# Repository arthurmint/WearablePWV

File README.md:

# WearablePWV
A wearable, wireless sensor for measuring pulse-wave velocity in humans

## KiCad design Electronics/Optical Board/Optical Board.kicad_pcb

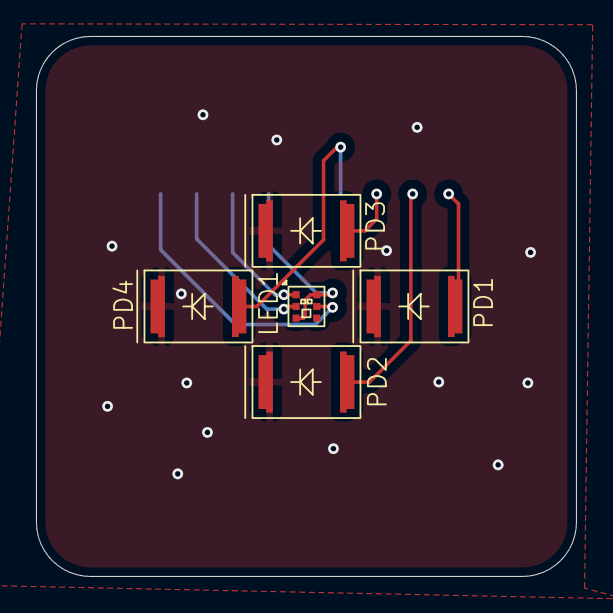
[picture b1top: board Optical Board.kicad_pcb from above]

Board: 2 copper layers, 30.0 x 30.0 mm, 6 parts (1 on the bottom side), 9 nets.

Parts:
J2: OPTICAL; JST_PH_S9B-PH-SM4-TB_1x09-1MP_P2.00mm_Horizontal
LED1: SFH-7016; SFH-7016 Multi Chip LED
PD1, PD2, PD3, PD4: SFH2200; TOPLED D5140

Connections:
+3V3: J2.4, LED1.2 (A), LED1.5 (A)
/LED1: J2.3, LED1.1 (KIR)
/LED2: J2.2, LED1.3 (KGREEN)
/LED3: J2.1, LED1.4 (KRED)
/PD1: J2.9, PD1.2 (A)
/PD2: J2.8, PD2.2 (A)
/PD3: J2.7, PD3.2 (A)
/PD4: J2.6, PD4.2 (A)
/PD_K: J2.5, PD1.1 (K), PD2.1 (K), PD3.1 (K), PD4.1 (K)

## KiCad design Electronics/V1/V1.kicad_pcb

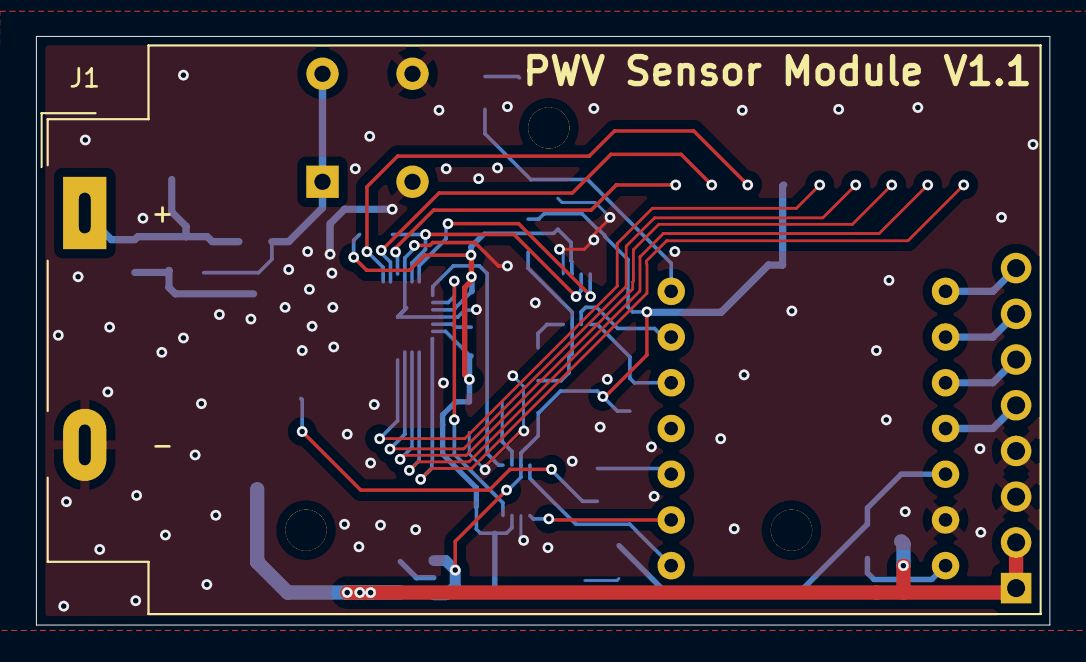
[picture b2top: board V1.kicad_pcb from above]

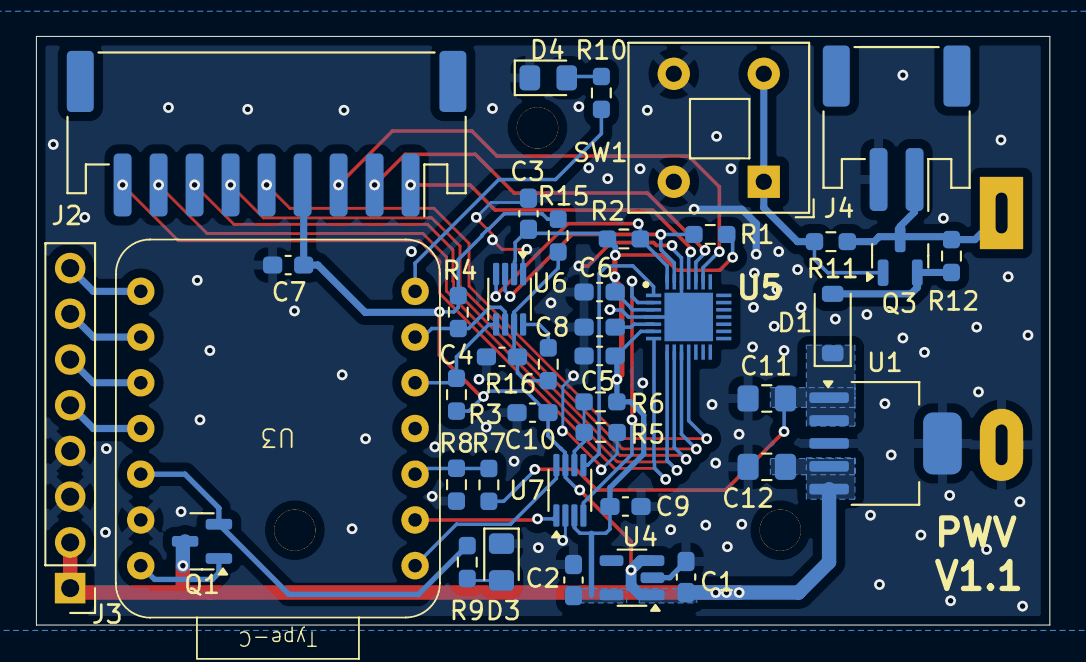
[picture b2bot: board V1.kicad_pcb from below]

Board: 2 copper layers, 56.3 x 32.7 mm, 42 parts (41 on the bottom side), 37 nets.

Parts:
C1, C8: 1u; C_0603_1608Metric_Pad1.08x0.95mm_HandSolder
C2: 10u; C_0603_1608Metric_Pad1.08x0.95mm_HandSolder
C3, C4, C5, C6, C9, C10: 100n; C_0603_1608Metric_Pad1.08x0.95mm_HandSolder
C7: 4u7; C_0603_1608Metric_Pad1.08x0.95mm_HandSolder
C11, C12: 10uF; C_0805_2012Metric_Pad1.18x1.45mm_HandSolder
D1: B130LAW-7-F; D_SOD-123
D3: 3V3 LED; LED_0805_2012Metric_Pad1.15x1.40mm_HandSolder
D4: CTRL LED; LED_0805_2012Metric_Pad1.15x1.40mm_HandSolder
J1: BA9VPC; BatteryHolder_MPD_BA9VPC_1xPP3
J2: OPTICAL; JST_PH_S9B-PH-SM4-TB_1x09-1MP_P2.00mm_Horizontal
J3: GPIO; PinHeader_1x08_P2.54mm_Vertical
J4: JST; JST_PH_S2B-PH-SM4-TB_1x02-1MP_P2.00mm_Horizontal
Q1, Q3: PMV41XPAR; SOT-23
R1, R2, R3, R4, R8, R11: 10k; R_0603_1608Metric_Pad0.98x0.95mm_HandSolder
R5: 200k; R_0603_1608Metric_Pad0.98x0.95mm_HandSolder
R6, R12: 0R; R_0603_1608Metric_Pad0.98x0.95mm_HandSolder
R7: 20k; R_0603_1608Metric_Pad0.98x0.95mm_HandSolder
R9, R10: 330; R_0603_1608Metric_Pad0.98x0.95mm_HandSolder
R15: 200K; R_0603_1608Metric_Pad0.98x0.95mm_HandSolder
R16: 0; R_0603_1608Metric_Pad0.98x0.95mm_HandSolder
SW1: PVA1 EE H1 3.5N V2; SW_Push_2P1T_Toggle_CK_PVA1xxH1xxxxxxV2
U1: TPS7A4533; SOT-223-6
U3: XIAO-ESP32-C3; Seeed Studio XIAO ESP32-C3
U4: TPS72218; SOT-23-5
U5: ADPD1080
U6: PCA9306DC; VSSOP-8_2.3x2mm_P0.5mm
U7: TXB0102DCU; VSSOP-8_2.3x2mm_P0.5mm

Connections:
+1V8: C2.1, C3.1, C5.1, C6.1, C9.1, R1.1, R2.1, R6.1, U4.5 (VOUT), U5.3 (DVDD), U5.6 (AVDD), U6.2 (VREF1), U7.3 (VCCA)
+3V3: C1.1, C7.1, C10.1, C12.1, J2.4, J3.1, J3.2, Q1.3 (D), R3.1, R4.1, R15.1, U1.4 (OUT), U1.5 (ADJ), U4.1 (VIN), U4.3 (EN), U7.7 (VCCB)
/AFE_0: U5.1 (GPIO0), U7.5 (A1)
/AFE_1: U5.2 (GPIO1), U7.4 (A2)
/BAT+: J1.1, J4.1, Q3.3 (D), R11.1, R12.1
/BAT_SENSE: R7.2, R8.1, U3.3 (D2)
/LED1: J2.3, U5.23 (LEDX1)
/LED2: J2.2, U5.24 (LEDX2)
/LED3: J2.1, U5.25 (LEDX3)
/PD1: J2.9, U5.7 (PD1)
/PD2: J2.8, U5.8 (PD2)
/PD3: J2.7, U5.9 (PD3)
/PD4: J2.6, U5.10 (PD4)
/PD_K: J2.5, U5.11 (PDC)
/PPG_SCL: R1.2, U5.27 (SCL), U6.3 (SCL1)
/PPG_SDA: R2.2, U5.28 (SDA), U6.4 (SDA1)
/UC_D0: U3.1 (D0), U7.8 (B1)
/UC_D1: U3.2 (D1), U7.1 (B2)
/UC_D6: R10.1, U3.7 (D6/TX)
/UC_D7: J3.8, U3.8 (D7/RX)
/UC_D8: J3.7, U3.9 (D8/SCK)
/UC_D9: J3.6, U3.10 (D9/MISO)
/UC_D10: J3.5, U3.11 (D10/MOSI)
/UC_SCL: R4.2, U3.6 (D5/SCL), U6.6 (SCL2)
/UC_SDA: R3.2, U3.5 (D4/SDA), U6.5 (SDA2)
GND: C1.2, C2.2, C3.2, C4.2, C5.2, C6.2, C7.2, C8.2, C9.2, C10.2, C11.2, C12.2, D3.1 (K), D4.1 (K), J1.2, J3.3, J3.4, J4.2, R5.2, R8.2, SW1.2, SW1.4, U1.3 (GND), U1.6 (GND), U3.13 (GND), U4.2 (GND), U5.4 (AGND), U5.26 (LGND), U5.29 (DGND), U6.1 (GND), U7.2 (GND)
unnamed: D1.2 (A), Q3.2 (S), R12.2
unnamed: D3.2 (A), R9.2
unnamed: D4.2 (A), R10.2
unnamed: Q1.2 (S), R9.1, U3.12 (3V3)
unnamed: Q3.1 (G), R11.2, SW1.1, SW1.3
unnamed: C8.1, U5.5 (VREF)
unnamed: R16.2, U6.8 (EN)
unnamed: C4.1, R15.2, R16.1, U6.7 (VREF2)
unnamed: R5.1, R6.2, U7.6 (OE)
VBAT: C11.1, D1.1 (K), R7.1, U1.1 (~SHDN), U1.2 (IN)
VUSB: Q1.1 (G), U3.14 (5V)

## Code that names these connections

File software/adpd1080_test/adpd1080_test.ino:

//working code
#include <Arduino.h>

#include "../include/pinout.h"
#include "../include/adpd1080.h"

ADPD1080 AFE;
uint32_t data;
/* Project specific functions -- define measurement procedure */

bool startMeasurement() {
  if (AFE.getMode() == AFE.STANDBY) {
    if (!AFE.clk32k_en(1)) {
      AFE.configurePPG(false); // configures and sets OPERATION internally
      // Now flush the FIFO after configuration
      AFE.setMode(AFE.PROGRAM);
      delay(10);
      AFE.setMode(AFE.OPERATION);
    }
    return false;

  } else if (AFE.getMode() == AFE.PROGRAM) {
    AFE.setMode(AFE.OPERATION);
    return false;

  } else {
    #ifdef DEBUG_OUTPUT
    Serial.println("Device not in STANDBY, cannot start measurement");
    #endif
    return true;
  }
}

void setup() { 
    Serial.begin(9600);
    delay(1000);
    
    AFE.begin(PIN_SDA, PIN_SCL, PIN_GPIO0, PIN_GPIO1);
    delay(500);
    
    AFE.printDevID(); // must be after begin()
    
    startMeasurement();
    AFE.readbackConfig(); 
  Serial.println("Initialised ADPD1080");
  //delay(10000);
}

void loop() {
  //uint16_t pd1, pd2, pd3, pd4;

  uint16_t available_data = (AFE.getStatus() >> 8) & 0xFF;
  //Serial.print("Available data: ");
  //Serial.print(available_data);

  if (available_data >= 4) {
    AFE.readFIFO(&data, 4);

    Serial.println(data);
    /*
    if (!AFE.readPPG(&pd1, &pd2, &pd3, &pd4)) {
      Serial.print(" PD1: "); Serial.print(pd1);
      Serial.print(" PD2: "); Serial.print(pd2);
      Serial.print(" PD3: "); Serial.print(pd3);
      Serial.print(" PD4: "); Serial.println(pd4);
    } else {
      Serial.println("Read error");
    }*/

    
  } else {
    //Serial.println(" - Not enough data");
  }

  delay(100);
}

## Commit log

2025-11-06 Added symbol for Xiao ESP32
2025-11-09 Added more symbols
2025-11-13 added capacitors and pull-up resistors
2025-11-14 Added footprint for ADPD144
2025-11-19 Added more symbols and footprints
2025-11-25 Added footprints for SFH-7016 and TOPLED
2025-11-25 Added level shifter for gpio, 5V reg, battery monitor and changed some footprints.
2025-11-27 Added Seeed Studio footprint
2025-12-03 Minor fixes
2025-12-05 Some unfinished PCB changes
2025-12-05 minor changes
2025-12-05 Swapped I2C shifter for PCA9306DC
2025-12-07 Changing from integrated optical sensors to separate PCB
2025-12-23 Footprint changes
2026-02-09 Add files via upload
    software files
2026-02-25 Work-in-progress, added pinout.h and test script
2026-02-26 adpd1080.h
2026-03-15 startMeasurement
2026-03-24 Progress with adpd1080, just need LED and photodiode headers
2026-04-03 LED pulse working, interrupt and polling reading added but not yet working.
2026-04-04 Create espseeed_host
2026-04-04 Create gg
2026-04-04 Untested: TIA ADC Mode. WIP
2026-04-06 Added some helpful comments to adpd1080.h
2026-04-06 Updated ,gitignore with .vscode
2026-04-06 Made it so that you can open pwvdissertation.ino in Arduino IDE
2026-04-08 Made setLED() more readable
2026-04-08 Added latency measurements to espseeed_host
2026-04-08 Small fixes to adpd1080.h
2026-04-08 Back in time
2026-04-16 PDs reading successfully
2026-04-21 Try different AFE connection
2026-04-29 Added Python Serial logging / plotting scripts and setup instructions
2026-04-29 Changes to the ADPD1080 to prevent it from saturating, see logbook
2026-05-10 Removed limits
2026-05-10 Average baseline readings
2026-05-10 Web Server changes
2026-05-10 Dual graph
2026-05-11 Added serialPlotter2.py
2026-05-11 Changed to IR LED and moved data out of loop
2026-05-11 Fixed dual graph
